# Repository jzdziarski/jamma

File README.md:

# /jamma
## Arcade JAMMA adapters and interface boards 
License: For non-commercial educational use only

|Subfolder|Description|
|--------------------------------|------------------------------------|
|CAD|PCB CAD Files|
|BOM|Bill of Materials (CSV)|
|Microcode|Microcontroller Code|
|Renderings|PCB Renderings|

## PCB Library
|Platform|Title|Tag|Status|
|-------------------|------------|-------------------------|----------|  
|Atari System I	|RoadBlasters|ROADBLASTERS_REV_0|Release|
|Atari System I |RoadBlasters|ROADBLASTERS_REV_1|Release|
|Atari System I/II/68K |*|ATARI_REV_0|Release|
|Atari System I/II/68K |*|ATARI_REV_1|Release|
|Blasteroids |Blasteroids|BLASTEROIDS_REV_0|Release|
|Midway MCR III	|Spy Hunter|SPY_HUNTER_REV_0|Release|
|Midway MCR III	|Spy Hunter|SPY_HUNTER_REV_1|Release|
|Midway MCR III |Spy Hunter|SPY_HUNTER_REV_1.1|Development|
|Midway MCR II	|TRON|TRON_REV_0|Release|
|Midway MCR II	|TRON|TRON_REV_1|Release|
|SEGA Super Scaler|Outrun|OUTRUN_REV_0|Release|
|SEGA Super Scaler|Super Hang-On|SUPER_HANG_ON_REV_0|Development|
|Williams System	|*|WILLIAMS_REV_0|Release|
|Williams System        |*|WILLIAMS_REV_1|Development|
|Universal Edge	|*|UNIVERSAL_EDGE|Release|
|Universal Interface|*|UNIVERSAL_INTERFACE|Release|
|Universal Microcontroller Interface|*|UNIVERSAL_MICROCONTROLLER|Template|
|Universal Microcontroller Adapter|*|UNIVERSAL_MICROCONTROLLER_ADAPTER|Template|

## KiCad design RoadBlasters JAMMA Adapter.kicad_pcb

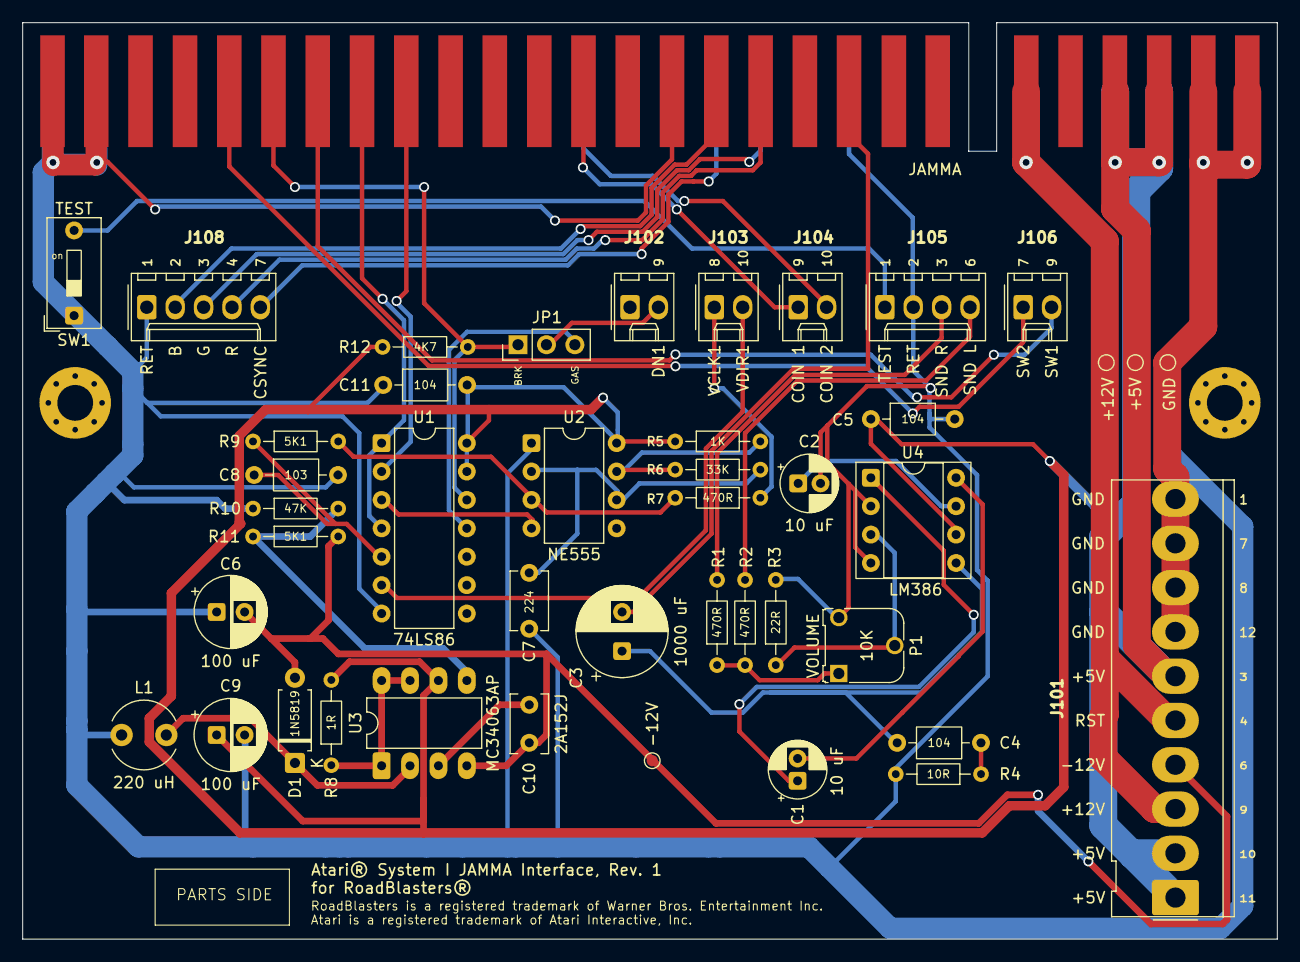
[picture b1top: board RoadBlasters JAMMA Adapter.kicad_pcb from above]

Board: 2 copper layers, 112.2 x 82.0 mm, 46 parts (0 on the bottom side), 39 nets.

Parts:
+5V: TP2; TestPoint_Pad_D1.0mm
+12V: TP3; TestPoint_Pad_D1.0mm
-12V: TP4; TestPoint_Pad_D1.0mm
C1, C2: 10 uF; CP_Radial_D5.0mm_P2.00mm
C3: 1000 uF; CP_Radial_D8.0mm_P3.50mm
C4, C5, C11: 104; C_Axial_L3.8mm_D2.6mm_P7.50mm_Horizontal
C6, C9: 100 uF; CP_Radial_D6.3mm_P2.50mm
C7: 224; C_Disc_D5.1mm_W3.2mm_P5.00mm
C8: 103; C_Axial_L3.8mm_D2.6mm_P7.50mm_Horizontal
C10: 2A152J; C_Disc_D5.1mm_W3.2mm_P3.4mm
D1: 1N5819; D_A-405_P7.62mm_Horizontal
GND: TP1; TestPoint_Pad_D1.0mm
J101: Molex_KK-396_5273-10A_1x10_P3.96mm_Vertical
J102, J103, J104, J106: Molex_KK-254_AE-6410-02A_1x02_P2.54mm_Vertical
J105: Molex_KK-254_AE-6410-04A_1x04_P2.54mm_Vertical
J108: Molex_KK-254_AE-6410-05A_1x05_P2.54mm_Vertical
JAMMA: HDR_JAMMA_56P_EDGE_CONNECTOR
JP1: PinHeader_1x03_P2.54mm_Vertical
L1: 220 uH; L_Radial_D6.0mm_P4.00mm
P1: 10K; Potentiometer_Runtron_RM-065_Vertical
PMH1, PMH4: MountingHole_3.2mm_M3_Pad_Via
R1: R1; R_Axial_DIN0204_L3.6mm_D1.6mm_P7.62mm_Horizontal
R2, R7: 470R; R_Axial_DIN0204_L3.6mm_D1.6mm_P7.62mm_Horizontal
R3: 22R; R_Axial_DIN0204_L3.6mm_D1.6mm_P7.62mm_Horizontal
R4: R_Axial_DIN0204_L3.6mm_D1.6mm_P7.62mm_Horizontal
R5: 1K; R_Axial_DIN0204_L3.6mm_D1.6mm_P7.62mm_Horizontal
R6: 33K; R_Axial_DIN0204_L3.6mm_D1.6mm_P7.62mm_Horizontal
R8: 1R; R_Axial_DIN0204_L3.6mm_D1.6mm_P7.62mm_Horizontal
R9, R11: 5K1; R_Axial_DIN0204_L3.6mm_D1.6mm_P7.62mm_Horizontal
R10: 47K; R_Axial_DIN0204_L3.6mm_D1.6mm_P7.62mm_Horizontal
R12: 4K7; R_Axial_DIN0204_L3.6mm_D1.6mm_P7.62mm_Horizontal
TEST: SW1; SW_DIP_SPSTx01_Slide_9.78x4.72mm_W7.62mm_P2.54mm
U1: 74LS86; DIP-14_W7.62mm
U2: NE555; DIP-8_W7.62mm
U3: MC34063AP; DIP-8_W7.62mm_LongPads
U4: LM386; DIP-8_W7.62mm_Socket

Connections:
1P_B1: J106.2, JAMMA.22
1P_B2: JAMMA.23, JP1.1, R12.2, U1.12
1P_B2_OUT: J102.2, JP1.2
1P_B3: J106.1, JAMMA.24
1P_L: JAMMA.20, U1.2
1P_R: JAMMA.21, U1.1, U1.4
!1P_B2: JP1.3, U1.11
+5V: +5V.1, C5.1, C9.1, C11.2, J101.1, J101.2, J101.6, JAMMA.3, JAMMA.4, JAMMA.C, JAMMA.D, R5.1, R8.2, R12.1, U1.13, U1.14, U2.8, U3.6, U4.6
+12V: +12V.1, J101.3, J101.5, JAMMA.6, JAMMA.F
-12V: -12V.1, C6.2, C10.1, D1.2, J101.4, R11.2, U3.4
AUDIO_L: J105.4, R2.2
AUDIO_MONO: P1.1, R1.1, R2.1
AUDIO_OUT: C3.2, JAMMA.10
AUDIO_PREAMP: P1.2, R3.1, U4.3
AUDIO_PREAMP_OUT: C3.1, C4.2, U4.5
AUDIO_R: J105.3, R1.2
C4_R4: C4.1, R4.1
CINV_R10_R9: R10.2, R11.1, U3.5
COIN_1: J104.1, JAMMA.16
COIN_2: J104.2, JAMMA.T
GND: C2.2, C5.2, C6.1, C7.1, C8.2, C9.2, C11.1, GND.1, J101.7, J101.8, J101.9, J101.10, J105.2, J108.1, JAMMA.1, JAMMA.2, JAMMA.14, JAMMA.27, JAMMA.28, JAMMA.A, JAMMA.B, JAMMA.L, JAMMA.e, JAMMA.f, L1.1, P1.3, R3.2, R4.2, R10.1, TEST.1, U1.7, U2.1, U4.2, U4.4
R8: R8.1, U3.1, U3.7, U3.8
SWE: D1.1, L1.2, U3.2
TEST_SW: J105.1, TEST.2
U2_DIS: R5.2, R6.1, U2.7
U2_RESET: U1.3, U2.4
U2_THR: C7.2, R6.2, U2.2, U2.6
U3_CAP: C10.2, U3.3
U4_BYPASS: C2.1, U4.7
U4_GAIN_P1: C1.1, U4.1
U4_GAIN_P8: C1.2, U4.8
VCLK1: R7.2, R9.2, U2.3
VCLK1_DELAYED: C8.1, R9.1, U1.5
VCLK1_OUT: J103.1, R7.1
VDIR1_OUT: J103.2, U1.6
VIDEO_B: J108.2, JAMMA.13
VIDEO_G: J108.3, JAMMA.N
VIDEO_R: J108.4, JAMMA.12
VIDEO_SYNC: J108.5, JAMMA.P

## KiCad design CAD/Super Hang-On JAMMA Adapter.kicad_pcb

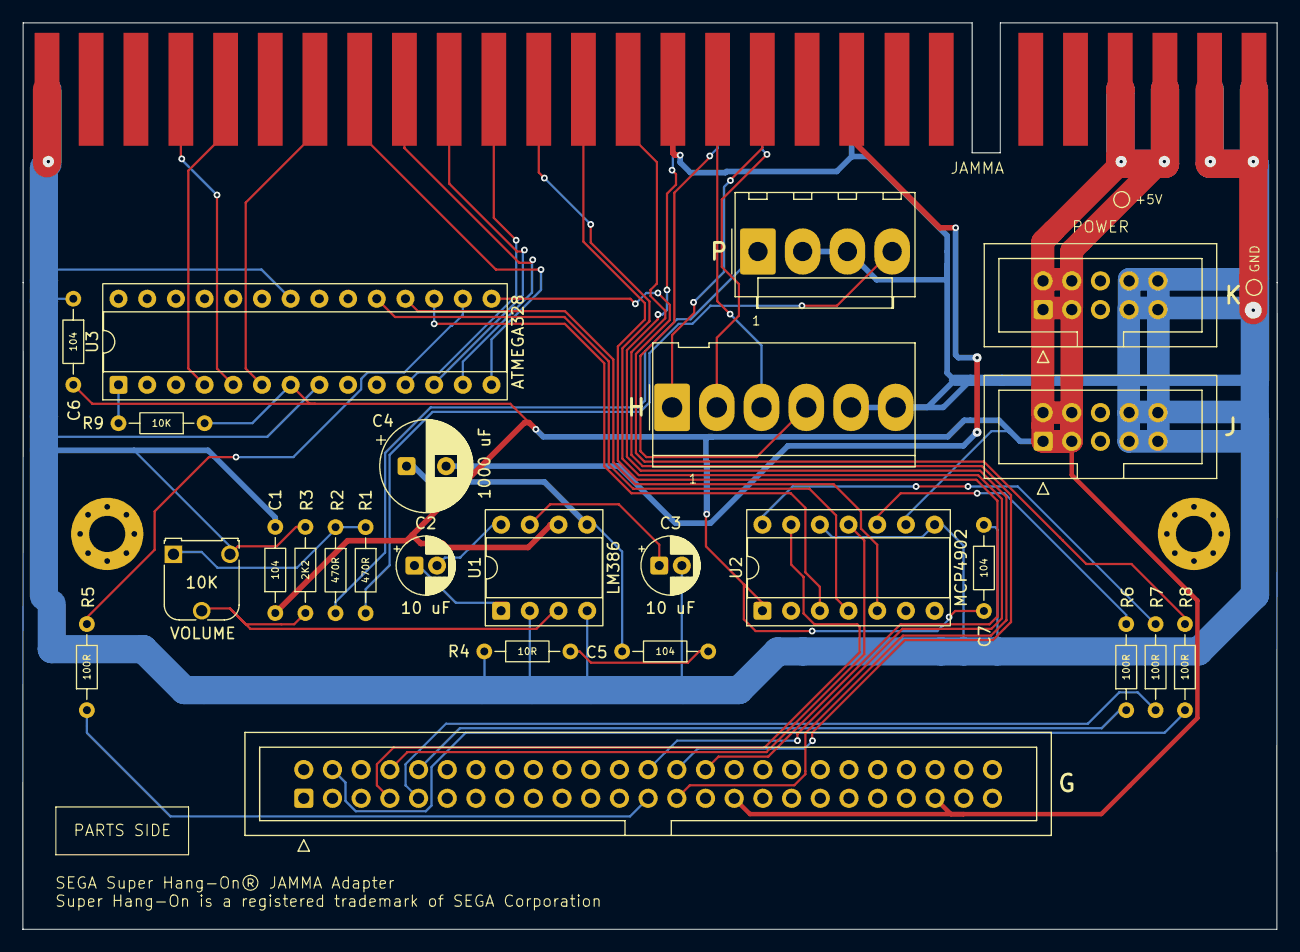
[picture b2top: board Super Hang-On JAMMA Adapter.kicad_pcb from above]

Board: 2 copper layers, 111.0 x 80.2 mm, 28 parts (0 on the bottom side), 41 nets.

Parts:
+5V: TestPoint_Pad_D1.0mm
C1, C5, C6, C7: 104; R_Axial_DIN0204_L3.6mm_D1.6mm_P7.62mm_Horizontal
C2, C3: 10 uF; CP_Radial_D5.0mm_P2.00mm
C4: 1000 uF; CP_Radial_D8.0mm_P3.50mm
G: G; IDC-Header_2x25_P2.54mm_Vertical
GND: TestPoint_Pad_D1.0mm
H: H; Molex_KK-396_5273-06A_1x06_P3.96mm_Vertical
J: J; IDC-Header_2x05_P2.54mm_Vertical
JAMMA: HDR_JAMMA_56P_EDGE_CONNECTOR
K: K; IDC-Header_2x05_P2.54mm_Vertical
P: P; Molex_KK-396_A-41791-0004_1x04_P3.96mm_Vertical
R1, R2: 470R; R_Axial_DIN0204_L3.6mm_D1.6mm_P7.62mm_Horizontal
R3: 2K2; R_Axial_DIN0204_L3.6mm_D1.6mm_P7.62mm_Horizontal
R4: 10R; R_Axial_DIN0204_L3.6mm_D1.6mm_P7.62mm_Horizontal
R5, R6, R7, R8: 100R; R_Axial_DIN0204_L3.6mm_D1.6mm_P7.62mm_Horizontal
R9: 10K; R_Axial_DIN0204_L3.6mm_D1.6mm_P7.62mm_Horizontal
U1: LM386; DIP-8_W7.62mm_Socket
U2: MCP4902; DIP-14_W7.62mm_Socket
U3: ATMEGA328; DIP-28_W7.62mm_Socket
VOLUME: 10K; Potentiometer_Runtron_RM-065_Vertical

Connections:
1P_B1: JAMMA.22, U3.6
1P_B3: JAMMA.24, U3.4
1P_B4: JAMMA.25, U3.5
1P_D: JAMMA.19, U3.12
1P_L: JAMMA.20, U3.13
1P_R: JAMMA.21, U3.14
1P_START: G.26, JAMMA.17
1P_U: JAMMA.18, U3.11
+5V: +5V.1, C1.1, C6.2, C7.2, G.31, G.45, J.1, J.2, J.3, J.4, JAMMA.3, JAMMA.4, JAMMA.C, JAMMA.D, K.1, K.2, K.3, K.4, R9.1, U1.6, U2.1, U2.9, U3.7
ACCEL: G.9, R7.1
AUDIO_L: P.1, R2.2
AUDIO_MONO: R1.1, R2.1, VOLUME.1
AUDIO_R: P.4, R1.2
BRK: G.4, R8.1
C5_R4: C5.1, R4.1
COIN_1: G.30, JAMMA.16
GND: C1.2, C3.2, C6.1, C7.1, GND.1, H.5, H.6, J.7, J.8, J.9, J.10, JAMMA.1, JAMMA.2, JAMMA.14, JAMMA.28, JAMMA.A, JAMMA.B, JAMMA.L, JAMMA.f, K.7, K.8, K.9, K.10, P.2, P.3, R3.2, R4.2, U1.2, U1.4, U2.8, U2.12, U3.8, U3.22, VOLUME.3
PB1: R8.2, U3.15
PB2: R5.2, U3.16
PREAMP: R3.1, U1.3, VOLUME.2
PREAMP_OUT: C4.1, C5.2, U1.5
REFA: G.7, U2.13
REFB: G.8, U2.11
SERVICE: G.27, JAMMA.R
SPKR+: C4.2, JAMMA.10
STEER: G.10, R6.1
TEST: G.28, JAMMA.15
TURBO: G.25, R5.1
U1_BYPASS: C3.1, U1.7
U1_GAIN_P1: C2.1, U1.1
U1_GAIN_P8: C2.2, U1.8
U3_MISO_U2_SDI: U2.5, U3.18
U3_MOSI_U2_CS: U2.3, U3.17
U3_RSET: R9.2, U3.1
U3_SCK_U2_SCK: U2.4, U3.19
VID_B: H.3, JAMMA.13
VID_CSYNC: H.4, JAMMA.P
VID_G: H.2, JAMMA.N
VID_R: H.1, JAMMA.12
VOUTA: R7.2, U2.14
VOUTB: R6.2, U2.10

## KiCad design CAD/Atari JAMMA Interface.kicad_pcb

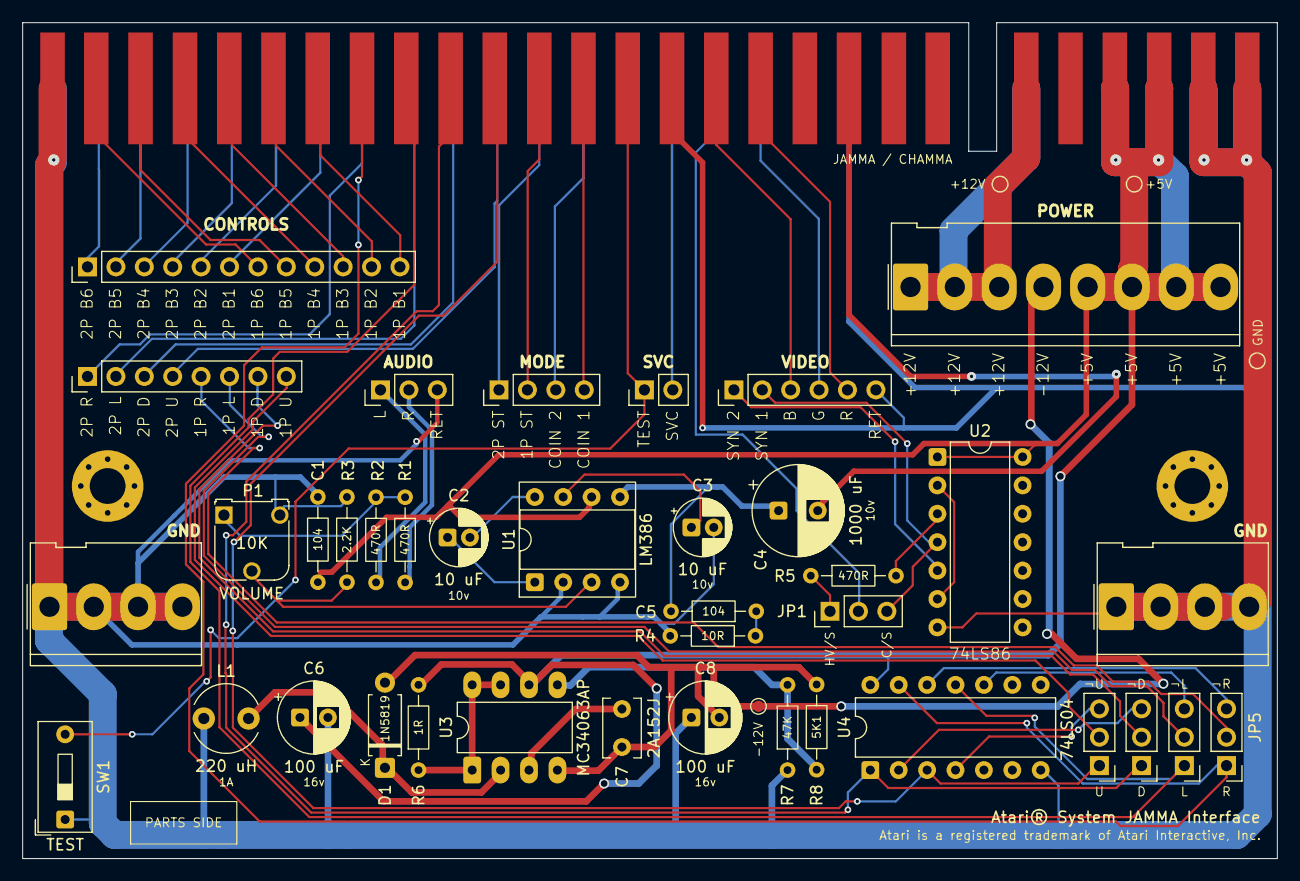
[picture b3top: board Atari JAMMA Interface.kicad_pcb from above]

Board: 2 copper layers, 112.2 x 74.8 mm, 43 parts (0 on the bottom side), 61 nets.

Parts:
+5V, +12V: TestPoint_Pad_D1.0mm
-12V: TestPoint_Pad_D1.0mm
AUDIO: PinHeader_1x03_P2.54mm_Vertical
C1, C5: 104; R_Axial_DIN0204_L3.6mm_D1.6mm_P7.62mm_Horizontal
C2, C3: 10 uF; CP_Radial_D5.0mm_P2.00mm
C4: 1000 uF; CP_Radial_D8.0mm_P3.50mm
C6, C8: 100 uF; CP_Radial_D6.3mm_P2.50mm
C7: 2A152J; C_Disc_D5.1mm_W3.2mm_P3.4mm
CONTROLS: PinHeader_1x12_P2.54mm_Vertical
D1: 1N5819; D_A-405_P7.62mm_Horizontal
DIRECTIONALS: PinHeader_1x08_P2.54mm_Vertical
GND: TestPoint_Pad_D1.0mm
GND#2, GND#3: Molex_KK-396_5273-04A_1x04_P3.96mm_Vertical
HV/S: PinHeader_1x03_P2.54mm_Vertical
HV/S#2, HV/S#3, HV/S#4, HV/S#5: PinHeader_1x03_P2.54mm_Vertical
JAMMA / CHAMMA: HDR_JAMMA_56P_EDGE_CONNECTOR
L1: 220 uH; L_Radial_D6.0mm_P4.00mm
MODE: PinHeader_1x04_P2.54mm_Vertical
P1: 10K; Potentiometer_Runtron_RM-065_Vertical
POWER: Molex_KK-396_5273-08A_1x08_P3.96mm_Vertical
R1, R2, R5: 470R; R_Axial_DIN0204_L3.6mm_D1.6mm_P7.62mm_Horizontal
R3: 2.2K; R_Axial_DIN0204_L3.6mm_D1.6mm_P7.62mm_Horizontal
R4: 10R; R_Axial_DIN0204_L3.6mm_D1.6mm_P7.62mm_Horizontal
R6: 1R; R_Axial_DIN0204_L3.6mm_D1.6mm_P7.62mm_Horizontal
R7: 47K; R_Axial_DIN0204_L3.6mm_D1.6mm_P7.62mm_Horizontal
R8: 5K1; R_Axial_DIN0204_L3.6mm_D1.6mm_P7.62mm_Horizontal
SVC: PinHeader_1x02_P2.54mm_Vertical
TEST: SW1; SW_DIP_SPSTx01_Slide_9.78x4.72mm_W7.62mm_P2.54mm
U1: LM386; DIP-8_W7.62mm_Socket
U2: DIP-14_W7.62mm
U3: MC34063AP; DIP-8_W7.62mm_LongPads
U4: 74LS04; DIP-14_W7.62mm
VIDEO: PinHeader_1x06_P2.54mm_Vertical

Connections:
1P_!D: HV/S#5.3, U4.2
1P_!L: HV/S.3, U4.10
1P_!R: HV/S#2.3, U4.12
1P_!U: HV/S#3.3, U4.4
1P_B1: CONTROLS.12, JAMMA / CHAMMA.22
1P_B2: CONTROLS.11, JAMMA / CHAMMA.23
1P_B3: CONTROLS.10, JAMMA / CHAMMA.24
1P_B4: CONTROLS.9, JAMMA / CHAMMA.25
1P_B5: CONTROLS.8, JAMMA / CHAMMA.26
1P_B6: CONTROLS.7, JAMMA / CHAMMA.27
1P_D: HV/S#5.1, JAMMA / CHAMMA.19, U4.1
1P_D_OUT: DIRECTIONALS.7, HV/S#5.2
1P_L: HV/S.1, JAMMA / CHAMMA.20, U4.11
1P_L_OUT: DIRECTIONALS.6, HV/S.2
1P_R: HV/S#2.1, JAMMA / CHAMMA.21, U4.13
1P_R_OUT: DIRECTIONALS.5, HV/S#2.2
1P_START: JAMMA / CHAMMA.17, MODE.2
1P_U: HV/S#3.1, JAMMA / CHAMMA.18, U4.3
1P_U_OUT: DIRECTIONALS.8, HV/S#3.2
2P_B1: CONTROLS.6, JAMMA / CHAMMA.Z
2P_B2: CONTROLS.5, JAMMA / CHAMMA.a
2P_B3: CONTROLS.4, JAMMA / CHAMMA.b
2P_B4: CONTROLS.3, JAMMA / CHAMMA.c
2P_B5: CONTROLS.2, JAMMA / CHAMMA.d
2P_B6: CONTROLS.1, JAMMA / CHAMMA.e
2P_D: DIRECTIONALS.3, JAMMA / CHAMMA.W
2P_L: DIRECTIONALS.2, JAMMA / CHAMMA.X
2P_R: DIRECTIONALS.1, JAMMA / CHAMMA.Y
2P_START: JAMMA / CHAMMA.U, MODE.1
2P_U: DIRECTIONALS.4, JAMMA / CHAMMA.V
+5V: +5V.1, C1.1, C6.1, JAMMA / CHAMMA.3, JAMMA / CHAMMA.4, JAMMA / CHAMMA.C, JAMMA / CHAMMA.D, POWER.5, POWER.6, POWER.7, POWER.8, R6.2, U1.6, U2.1, U2.14, U3.6, U4.14
+12V: +12V.1, JAMMA / CHAMMA.6, JAMMA / CHAMMA.F, POWER.1, POWER.2, POWER.3
-12V: -12V.1, C7.1, C8.2, D1.2, POWER.4, R8.2, U3.4
AUDIO_L: AUDIO.1, R2.2
AUDIO_MONO: P1.1, R1.1, R2.1
AUDIO_R: AUDIO.2, R1.2
C5_R4: C5.1, R4.1
CINV_R10_R9: R7.2, R8.1, U3.5
COIN_1: JAMMA / CHAMMA.16, MODE.4
COIN_2: JAMMA / CHAMMA.T, MODE.3
GND: AUDIO.3, C1.2, C3.2, C6.2, C8.1, GND.1, GND#2.1, GND#2.2, GND#2.3, GND#2.4, GND#3.1, GND#3.2, GND#3.3, GND#3.4, JAMMA / CHAMMA.1, JAMMA / CHAMMA.2, JAMMA / CHAMMA.14, JAMMA / CHAMMA.28, JAMMA / CHAMMA.A, JAMMA / CHAMMA.B, JAMMA / CHAMMA.L, JAMMA / CHAMMA.f, L1.1, P1.3, R3.2, R4.2, R7.1, TEST.1, U1.2, U1.4, U2.7, U4.7, VIDEO.6
PREAMP: P1.2, R3.1, U1.3
PREAMP_OUT: C4.1, C5.2, U1.5
R8: R6.1, U3.1, U3.7, U3.8
SERVICE: JAMMA / CHAMMA.R, SVC.2
SPKR+: C4.2, JAMMA / CHAMMA.10
SWE: D1.1, L1.2, U3.2
TEST: JAMMA / CHAMMA.15, SVC.1, TEST.2
U3_CAP: C7.2, U3.3
U4_BYPASS: C3.1, U1.7
U4_GAIN_P1: C2.1, U1.1
U4_GAIN_P8: C2.2, U1.8
VID_B: JAMMA / CHAMMA.13, VIDEO.3
VID_CSYNC: HV/S#4.2, JAMMA / CHAMMA.P
VID_G: JAMMA / CHAMMA.N, VIDEO.4
VID_NXOR: HV/S#4.1, R5.1
VID_NXOR_R5: R5.2, U2.3
VID_R: JAMMA / CHAMMA.12, VIDEO.5
VID_SYN1: HV/S#4.3, U2.4, VIDEO.2
VID_SYN2: U2.5, VIDEO.1
VID_XOR: U2.2, U2.6

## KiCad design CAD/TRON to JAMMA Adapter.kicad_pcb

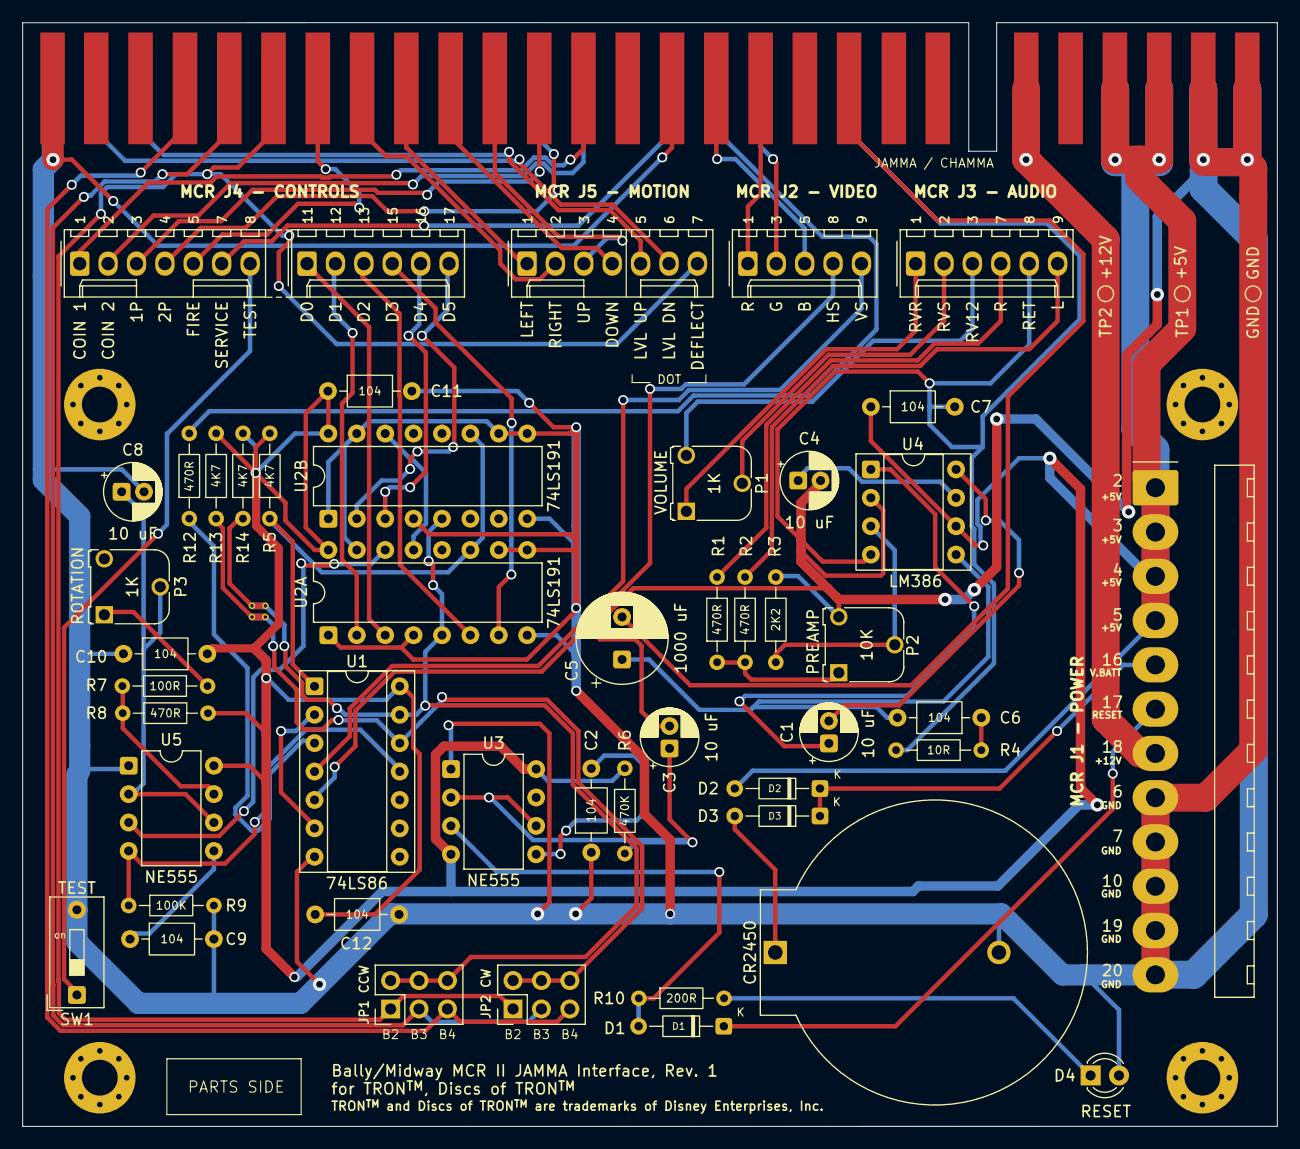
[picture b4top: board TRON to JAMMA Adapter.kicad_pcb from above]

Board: 2 copper layers, 112.2 x 98.7 mm, 56 parts (0 on the bottom side), 63 nets.

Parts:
+5V: TP1; TestPoint_Pad_D1.0mm
+12V: TP2; TestPoint_Pad_D1.0mm
C1, C3, C4, C8: 10 uF; CP_Radial_D5.0mm_P2.00mm
C2, C6, C7, C9, C10, C11, C12: 104; C_Axial_L3.8mm_D2.6mm_P7.50mm_Horizontal
C5: 1000 uF; CP_Radial_D8.0mm_P3.80mm
CR2450: BatteryHolder_ComfortableElectronic_CH273-2450_1x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; BatteryHolder_ComfortableElectronic_CH273-2450_1x2450
D1: 1N4148; D_DO-34_SOD68_P7.62mm_Horizontal
D2, D3: 1N5817; D_DO-34_SOD68_P7.62mm_Horizontal
D4: LED; LED_D3.0mm
GND: GND; TestPoint_Pad_D1.0mm
JAMMA / CHAMMA: HDR_JAMMA_56P_EDGE_CONNECTOR
JP1 CCW, JP2 CW: PinHeader_2x03_P2.54mm_Vertical
MCRJ1: Molex_KK-396_A-41792-0012_1x12_P3.96mm_Horizontal
MCRJ2: Molex_KK-254_AE-6410-05A_1x05_P2.54mm_Vertical
MCRJ3, MCRJ4B: Molex_KK-254_AE-6410-06A_1x06_P2.54mm_Vertical
MCRJ4A, MCRJ5: Molex_KK-254_AE-6410-07A_1x07_P2.54mm_Vertical
P1, P3: 1K; Potentiometer_Runtron_RM-065_Vertical
P2: 10K; Potentiometer_Runtron_RM-065_Vertical
PMH1, PMH2, PMH3, PMH4: MountingHole_3.2mm_M3_Pad_Via
R1, R2, R8, R12: 470R; R_Axial_DIN0204_L3.6mm_D1.6mm_P7.62mm_Horizontal
R3: 2K2; R_Axial_DIN0204_L3.6mm_D1.6mm_P7.62mm_Horizontal
R4: 10R; R_Axial_DIN0204_L3.6mm_D1.6mm_P7.62mm_Horizontal
R5, R13, R14: 4K7; R_Axial_DIN0204_L3.6mm_D1.6mm_P7.62mm_Horizontal
R6: 470K; R_Axial_DIN0204_L3.6mm_D1.6mm_P7.62mm_Horizontal
R7: 100R; R_Axial_DIN0204_L3.6mm_D1.6mm_P7.62mm_Horizontal
R9: 100K; R_Axial_DIN0204_L3.6mm_D1.6mm_P7.62mm_Horizontal
R10: 200R; R_Axial_DIN0204_L3.6mm_D1.6mm_P7.62mm_Horizontal
TEST: SW1; SW_DIP_SPSTx01_Slide_9.78x4.72mm_W7.62mm_P2.54mm
U1: 74LS86; DIP-14_W7.62mm_Socket
U2A, U2B: 74LS191; DIP-16_W7.62mm
U3, U5: NE555; DIP-8_W7.62mm
U4: LM386; DIP-8_W7.62mm_Socket

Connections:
1P_B1: JAMMA / CHAMMA.22, MCRJ4A.5
1P_B2: JAMMA / CHAMMA.23, JP1 CCW.1, JP2 CW.1, MCRJ5.7
1P_B3: JAMMA / CHAMMA.24, JP1 CCW.3, JP2 CW.3
1P_B4: JAMMA / CHAMMA.25, JP1 CCW.5, JP2 CW.5
1P_B5: JAMMA / CHAMMA.d, MCRJ5.5
1P_B6: JAMMA / CHAMMA.e, MCRJ5.6
1P_D: JAMMA / CHAMMA.19, MCRJ5.4
1P_L: JAMMA / CHAMMA.20, MCRJ5.1
1P_R: JAMMA / CHAMMA.21, MCRJ5.2
1P_START: JAMMA / CHAMMA.17, MCRJ4A.3
1P_U: JAMMA / CHAMMA.18, MCRJ5.3
2P_START: JAMMA / CHAMMA.U, MCRJ4A.4
+5V: +5V.1, C7.1, C10.2, C11.1, C12.2, D2.2, JAMMA / CHAMMA.3, JAMMA / CHAMMA.4, JAMMA / CHAMMA.C, JAMMA / CHAMMA.D, MCRJ1.1, MCRJ1.2, MCRJ1.3, MCRJ1.4, R5.2, R6.2, R8.2, R13.2, R14.2, U1.14, U2A.16, U2B.16, U3.4, U3.8, U4.6, U5.8
+5V_R5: R5.1, U1.1, U2A.11, U2B.11
+12V_IN: +12V.1, JAMMA / CHAMMA.6, JAMMA / CHAMMA.F, MCRJ1.7
AUDIO_L: MCRJ3.6, R2.2
AUDIO_MONO: P2.1, R1.1, R2.1
AUDIO_OUT: C5.2, JAMMA / CHAMMA.10
AUDIO_PREAMP: P2.2, R3.1, U4.3
AUDIO_PREAMP_OUT: C5.1, C6.2, U4.5
AUDIO_R: MCRJ3.4, R1.2
BATTERY: CR2450.1, D3.2
C6_R4: C6.1, R4.1
CCW_IN: JP1 CCW.2, JP1 CCW.4, JP1 CCW.6, U1.13, U2A.5, U2B.5
CLK: U2A.14, U5.3
CLK_GATE: R9.1, U1.11, U5.4
COIN_1: JAMMA / CHAMMA.16, MCRJ4A.1
COIN_2: JAMMA / CHAMMA.T, MCRJ4A.2
CW_IN: JP2 CW.2, JP2 CW.4, JP2 CW.6, U1.12
E1: MCRJ4B.1, U2A.3
E2: MCRJ4B.2, U2A.2
E3: MCRJ4B.3, U2A.6
E4: MCRJ4B.4, U2A.7
E5: MCRJ4B.5, U2B.3
E6: MCRJ4B.6, U2B.2
GND: C2.1, C3.2, C4.2, C7.2, C8.2, C9.2, C10.1, C11.2, C12.1, CR2450.2, D4.2, GND.1, JAMMA / CHAMMA.1, JAMMA / CHAMMA.2, JAMMA / CHAMMA.14, JAMMA / CHAMMA.28, JAMMA / CHAMMA.A, JAMMA / CHAMMA.B, JAMMA / CHAMMA.L, JAMMA / CHAMMA.f, MCRJ1.8, MCRJ1.9, MCRJ1.10, MCRJ1.11, MCRJ1.12, MCRJ3.5, P2.3, R3.2, R4.2, R9.2, TEST.2, U1.7, U2A.1, U2A.4, U2A.8, U2A.9, U2A.10, U2A.15, U2B.1, U2B.4, U2B.8, U2B.9, U2B.10, U2B.15, U3.1, U4.2, U4.4, U5.1
R6_U3_P2_P6: C3.1, R6.1, U3.2, U3.6
RESET_5V: D1.2, R10.1, U3.3
RESET_5V_OUT: D1.1, MCRJ1.6
RESET_LED: D4.1, R10.2
SERVICE_SW: JAMMA / CHAMMA.R, MCRJ4A.6
TEST_SW: MCRJ4A.7, TEST.1
U1_P6_U1_P2: U1.2, U1.6
U3_CTRL: C2.2, U3.5
U4_BYPASS: C4.1, U4.7
U4_GAIN_P1: C1.1, U4.1
U4_GAIN_P8: C1.2, U4.8
U5_CTRL: C9.1, U5.5
U5_DIS: R7.1, R8.1, U5.7
U5_DIS_R2: P3.1, R7.2
U5_TRIG: C8.1, P3.2, U5.2, U5.6
U6_RCO: U2A.13, U2B.14
V.BATT: D2.1, D3.1, MCRJ1.5
VIDEO_B: JAMMA / CHAMMA.13, MCRJ2.3
VIDEO_G: JAMMA / CHAMMA.N, MCRJ2.2
VIDEO_HSYNC: MCRJ2.4, U1.5
VIDEO_RED: JAMMA / CHAMMA.12, MCRJ2.1
VIDEO_SYNC: JAMMA / CHAMMA.P, R12.2
VIDEO_SYNC_R12: R12.1, U1.3
VIDEO_VSYNC: MCRJ2.5, U1.4
VOL_GND: MCRJ3.3, P1.3
VOL_IN: MCRJ3.1, P1.1
VOL_OUT: MCRJ3.2, P1.2

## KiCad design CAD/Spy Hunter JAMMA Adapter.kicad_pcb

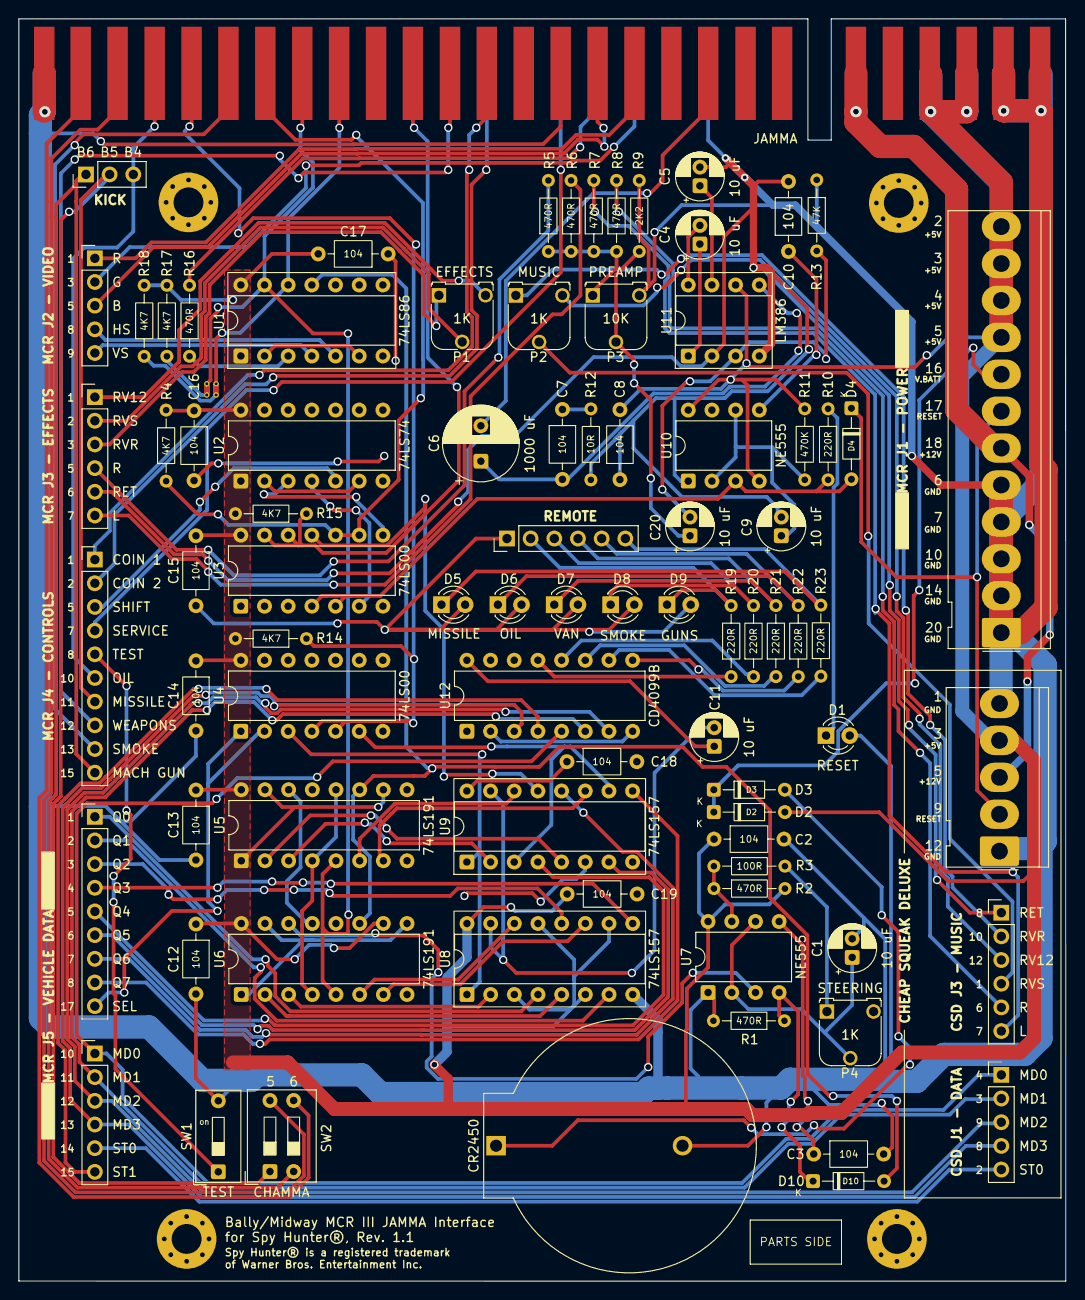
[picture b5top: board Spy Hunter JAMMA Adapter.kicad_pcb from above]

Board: 2 copper layers, 112.3 x 135.4 mm, 88 parts (0 on the bottom side), 102 nets.

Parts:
C1, C4, C5, C9, C11, C20: 10 uF; CP_Radial_D5.0mm_P2.00mm
C2, C3, C7, C8, C10, C12, C13, C14, C15, C16, C17, C18, C19: 104; C_Axial_L3.8mm_D2.6mm_P7.50mm_Horizontal
C6: 1000 uF; CP_Radial_D8.0mm_P3.80mm
CR2450: BatteryHolder_ComfortableElectronic_CH273-2450_1x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; BatteryHolder_ComfortableElectronic_CH273-2450_1x2450
CSDJ1: PinHeader_1x05_P2.54mm_Vertical
CSDJ2: Molex_KK-396_5273-05A_1x05_P3.96mm_Vertical
CSDJ3: PinHeader_1x06_P2.54mm_Vertical
D1, D5, D6, D7, D8, D9: LED; LED_D3.0mm
D2, D3: 1N5817; D_DO-34_SOD68_P7.62mm_Horizontal
D4, D10: 1N4148; D_DO-34_SOD68_P7.62mm_Horizontal
JAMMA: HDR_JAMMA_56P_EDGE_CONNECTOR
KICK: PinHeader_1x03_P2.54mm_Vertical
MCR J5 - LAMPS: PinHeader_1x06_P2.54mm_Vertical
MCRJ1: Molex_KK-396_5273-12A_1x12_P3.96mm_Vertical
MCRJ2: PinHeader_1x05_P2.54mm_Vertical
MCRJ3: PinHeader_1x06_P2.54mm_Vertical
MCRJ4: PinHeader_1x10_P2.54mm_Vertical
MCRJ5: PinHeader_1x09_P2.54mm_Vertical
P1, P2, P4: 1K; Potentiometer_Runtron_RM-065_Vertical
P3: 10K; Potentiometer_Runtron_RM-065_Vertical
PMH1, PMH2, PMH3, PMH4: MountingHole_3.2mm_M3_Pad_Via
R1, R2, R5, R6, R7, R8, R16: 470R; R_Axial_DIN0204_L3.6mm_D1.6mm_P7.62mm_Horizontal
R3: 100R; R_Axial_DIN0204_L3.6mm_D1.6mm_P7.62mm_Horizontal
R4, R14, R15, R17, R18: 4K7; R_Axial_DIN0204_L3.6mm_D1.6mm_P7.62mm_Horizontal
R9: 2K2; R_Axial_DIN0204_L3.6mm_D1.6mm_P7.62mm_Horizontal
R10, R19, R20, R21, R22, R23: 220R; R_Axial_DIN0204_L3.6mm_D1.6mm_P7.62mm_Horizontal
R11: 470K; R_Axial_DIN0204_L3.6mm_D1.6mm_P7.62mm_Horizontal
R12: 10R; R_Axial_DIN0204_L3.6mm_D1.6mm_P7.62mm_Horizontal
R13: 47K; R_Axial_DIN0204_L3.6mm_D1.6mm_P7.62mm_Horizontal
REMOTE: PinHeader_1x06_P2.54mm_Vertical
SW2: SW_DIP_SPSTx02_Slide_9.78x7.26mm_W7.62mm_P2.54mm
TEST: SW1; SW_DIP_SPSTx01_Slide_9.78x4.72mm_W7.62mm_P2.54mm
U1: 74LS86; DIP-14_W7.62mm_Socket
U2: 74LS74; DIP-14_W7.62mm
U3, U4: 74LS00; DIP-14_W7.62mm
U5, U6: 74LS191; DIP-16_W7.62mm
U7, U10: NE555; DIP-8_W7.62mm
U8, U9: 74LS157; DIP-16_W7.62mm_Socket
U11: LM386; DIP-8_W7.62mm_Socket
U12: CD4099B; DIP-16_W7.62mm

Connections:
1P_B1: JAMMA.22, R4.1, U3.9, U3.10
1P_B2: JAMMA.23, MCRJ4.9
1P_B3: JAMMA.24, R14.1, U4.4, U4.5
1P_B4: JAMMA.25, KICK.3, MCRJ4.6
1P_B5: KICK.2, MCRJ4.7, SW2.1
1P_B5_CHAMMA: JAMMA.26, SW2.4
1P_B6: KICK.1, MCRJ4.10, SW2.2
1P_B6_CHAMMA: JAMMA.27, SW2.3
1P_GAS: U4.6, U9.3, U9.10
1P_LEFT: JAMMA.20, U1.12
1P_RIGHT: JAMMA.21, U1.13, U5.5, U6.5
1P_START: JAMMA.17, MCRJ4.8
1P_TURBO: U3.11, U9.13
1P_U: JAMMA.18, R15.1, U3.12, U3.13
!RST: U2.4, U3.6
!SEL: U4.3, U8.1, U9.1
!SHIFT_LATCH: U2.2, U2.6
+5V: C2.1, C8.2, C11.1, C12.1, C13.1, C14.1, C15.1, C16.1, C17.2, C18.1, C19.1, CSDJ2.4, D2.2, JAMMA.3, JAMMA.4, JAMMA.C, JAMMA.D, MCRJ1.9, MCRJ1.10, MCRJ1.11, MCRJ1.12, R2.2, R4.2, R11.2, R14.2, R15.2, R17.2, R18.2, U1.1, U1.14, U2.1, U2.14, U3.14, U4.14, U5.1, U5.10, U5.15, U5.16, U6.10, U6.16, U7.8, U8.3, U8.6, U8.10, U8.13, U8.16, U9.6, U9.16, U10.4, U10.8, U11.6, U12.16
+5V_RST: CSDJ2.2, D4.1, MCRJ1.7
+12V: CSDJ2.3, JAMMA.6, JAMMA.F, MCRJ1.6
AUDIO_MONO: P3.1, R5.1, R6.1, R7.1, R8.1
AUDIO_OUT: C6.2, JAMMA.10
AUDIO_PREAMP: C20.1, P3.2, R9.1
AUDIO_PREAMP_COUPLED: C20.2, R13.2, U11.3
AUDIO_PREAMP_OUT: C6.1, C7.2, U11.5
BATT+: CR2450.1, D3.2
C7_R12: C7.1, R12.1
CLK: U6.14, U7.3
CLK_GATE: D10.2, U1.11, U5.11, U6.11
COIN_1: JAMMA.16, MCRJ4.1
COIN_2: JAMMA.T, MCRJ4.2
D5: D5.1, R23.2, REMOTE.6
D6: D6.1, R22.2, REMOTE.5
D7: D7.1, R21.2, REMOTE.4
D8: D8.1, R20.2, REMOTE.3
D9: D9.1, R19.2, REMOTE.2
EFFECTS_L: MCRJ3.6, R6.2
EFFECTS_R: MCRJ3.4, R5.2
EFFECTS_RV12: MCRJ3.1, P1.3
EFFECTS_RVR: MCRJ3.3, P1.1
EFFECTS_RVS: MCRJ3.2, P1.2
GND: C1.2, C2.2, C3.2, C5.2, C8.1, C9.2, C10.2, C11.2, C12.2, C13.2, C14.2, C15.2, C16.2, C17.1, C18.2, C19.2, CR2450.2, CSDJ2.1, CSDJ2.5, CSDJ3.1, D1.2, D5.2, D6.2, D7.2, D8.2, D9.2, JAMMA.1, JAMMA.2, JAMMA.14, JAMMA.28, JAMMA.A, JAMMA.B, JAMMA.L, JAMMA.f, MCRJ1.1, MCRJ1.2, MCRJ1.3, MCRJ1.4, MCRJ1.5, MCRJ3.5, P3.3, R1.2, R9.2, R12.2, R13.1, REMOTE.1, TEST.2, U1.7, U2.7, U3.7, U4.7, U5.8, U5.9, U6.1, U6.8, U6.9, U6.15, U7.1, U8.8, U8.15, U9.8, U9.15, U10.1, U11.2, U11.4, U12.2, U12.8
J5_ST0: CSDJ1.5, MCR J5 - LAMPS.5
MAXMIN_CTEN: U5.4, U5.12, U6.4
MUSIC_L: CSDJ3.6, R7.2
MUSIC_R: CSDJ3.5, R8.2
MUSIC_RV12: CSDJ3.3, P2.3
MUSIC_RVR: CSDJ3.2, P2.1
MUSIC_RVS: CSDJ3.4, P2.2
Q0: MCRJ5.1, U8.4
Q1: MCRJ5.2, U8.7
Q2: MCRJ5.3, U8.12
Q3: MCRJ5.4, U8.9
Q4: MCRJ5.5, U9.4
Q5: MCRJ5.6, U9.7
Q6: MCRJ5.7, U9.12
Q7: MCRJ5.8, U9.9
RST: D4.2, R10.1, U3.4, U3.5, U10.3
RST_LED: D1.1, R10.2
SEL: MCRJ5.9, U4.1, U4.2
SERVICE_SW: JAMMA.R, MCRJ4.4
SHIFT_LATCH: MCRJ4.3, U2.5
TEST_SW: MCRJ4.5, TEST.1
U2_CLK: U2.3, U3.8
U6_RCO: U5.14, U6.13
U7_CTL: C3.1, U7.5
U7_DIS: R2.1, R3.1, U7.7
U7_DIS_P4_1: P4.1, R3.2
U7_RESET: D10.1, R1.1, U7.4
U7_TRIG: C1.1, P4.2, U7.2, U7.6
U8_I0a: U6.3, U8.2
U8_I0b: U6.2, U8.5
U8_I0c: U6.6, U8.14
U8_I0d: U6.7, U8.11
U9_I0a: U5.3, U9.2
U9_I0b: U5.2, U9.5
U9_I0c: U5.6, U9.14
U9_I0d: U5.7, U9.11
U10_CTL: C10.1, U10.5
U10_TRIG: C9.1, R11.1, U10.2, U10.6
U11_BYPASS: C5.1, U11.7
U11_GAIN_P1: C4.1, U11.1
U11_GAIN_P8: C4.2, U11.8
U12_A0: CSDJ1.1, MCR J5 - LAMPS.1, U12.5
U12_A1: CSDJ1.2, MCR J5 - LAMPS.2, U12.6
U12_A2: CSDJ1.3, MCR J5 - LAMPS.3, U12.7
U12_DATA: CSDJ1.4, MCR J5 - LAMPS.4, U12.3
U12_DISABLE: MCR J5 - LAMPS.6, U12.4
U12_Q0: R22.1, U12.9
U12_Q1: R23.1, U12.10
U12_Q2: R21.1, U12.11
U12_Q3: R20.1, U12.12
U12_Q4: R19.1, U12.13
V.BATT: D2.1, D3.1, MCRJ1.8
VIDEO_B: JAMMA.13, MCRJ2.3
VIDEO_G: JAMMA.N, MCRJ2.2
VIDEO_HSYNC: MCRJ2.4, U1.5
VIDEO_NXOR: R16.1, U1.3
VIDEO_R: JAMMA.12, MCRJ2.1
VIDEO_SYNC_OUT: JAMMA.P, R16.2
VIDEO_VSYNC: MCRJ2.5, U1.4
VIDEO_XOR: U1.2, U1.6

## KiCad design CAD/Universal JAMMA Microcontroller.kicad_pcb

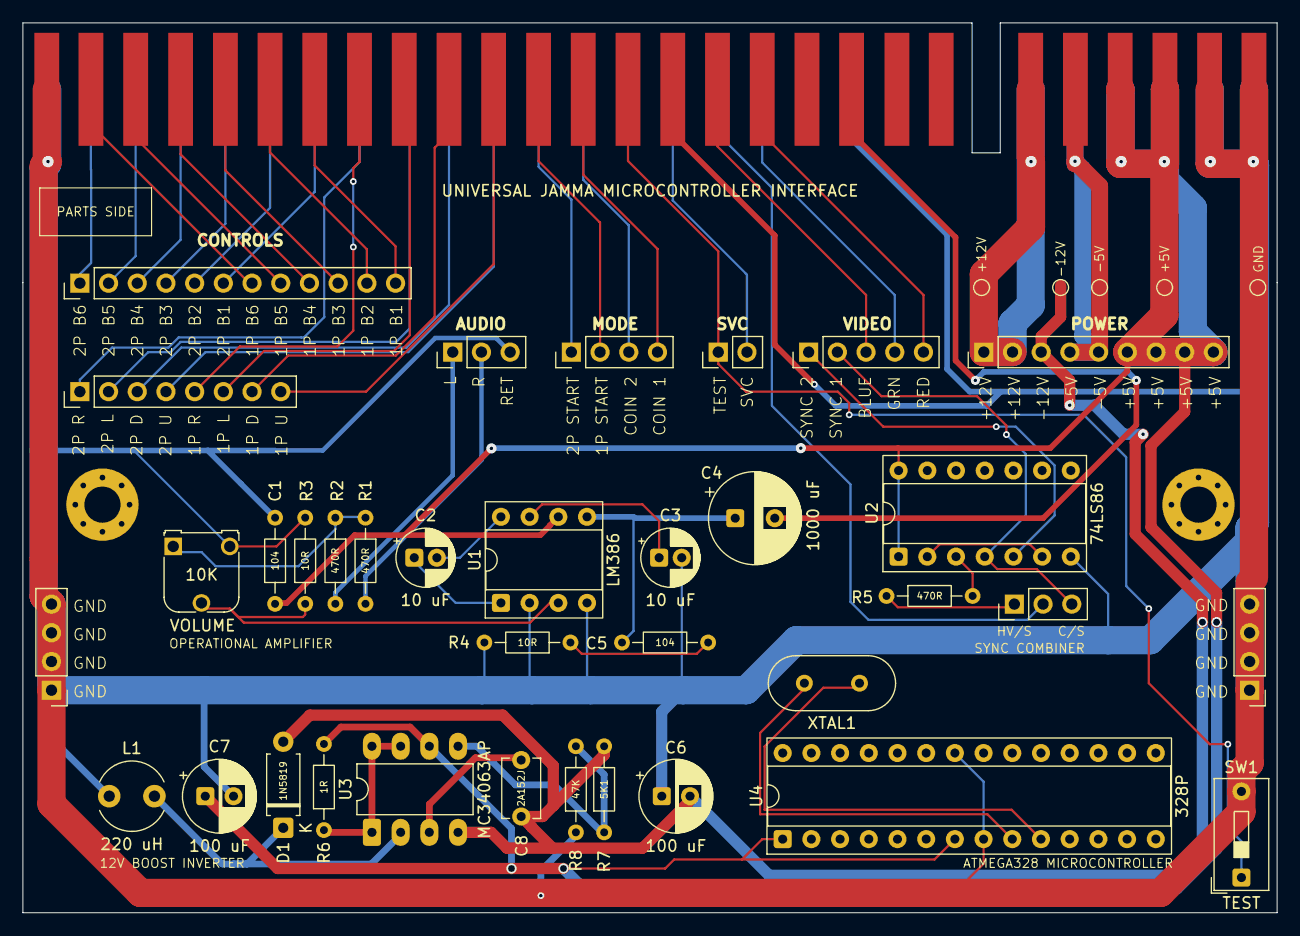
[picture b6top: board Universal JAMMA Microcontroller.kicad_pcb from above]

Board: 2 copper layers, 111.0 x 78.8 mm, 41 parts (0 on the bottom side), 56 nets.

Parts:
+5V, +12V: TestPoint_Pad_D1.0mm
-5V, -12V: TestPoint_Pad_D1.0mm
AUDIO: PinHeader_1x03_P2.54mm_Vertical
C1, C5: 104; R_Axial_DIN0204_L3.6mm_D1.6mm_P7.62mm_Horizontal
C2, C3: 10 uF; CP_Radial_D5.0mm_P2.00mm
C4: 1000 uF; CP_Radial_D8.0mm_P3.50mm
C6, C7: 100 uF; CP_Radial_D6.3mm_P2.50mm
C8: 2A152J; C_Disc_D5.1mm_W3.2mm_P5.00mm
CONTROLS: PinHeader_1x12_P2.54mm_Vertical
D1: 1N5819; D_A-405_P7.62mm_Horizontal
DIRECTIONALS: PinHeader_1x08_P2.54mm_Vertical
GND: TestPoint_Pad_D1.0mm
Ground: PinHeader_1x04_P2.54mm_Vertical
Ground#2: PinHeader_1x04_P2.54mm_Vertical
HV/S: PinHeader_1x03_P2.54mm_Vertical
JAMMA: HDR_JAMMA_56P_EDGE_CONNECTOR
L1: 220 uH; L_Radial_D6.0mm_P4.00mm
MODE: PinHeader_1x04_P2.54mm_Vertical
POWER: PinHeader_1x09_P2.54mm_Vertical
R1, R2, R5: 470R; R_Axial_DIN0204_L3.6mm_D1.6mm_P7.62mm_Horizontal
R3, R4: 10R; R_Axial_DIN0204_L3.6mm_D1.6mm_P7.62mm_Horizontal
R6: 1R; R_Axial_DIN0204_L3.6mm_D1.6mm_P7.62mm_Horizontal
R7: 5K1; R_Axial_DIN0204_L3.6mm_D1.6mm_P7.62mm_Horizontal
R8: 47K; R_Axial_DIN0204_L3.6mm_D1.6mm_P7.62mm_Horizontal
SVC: PinHeader_1x02_P2.54mm_Vertical
TEST: SW1; SW_DIP_SPSTx01_Slide_9.78x4.72mm_W7.62mm_P2.54mm
U1: LM386; DIP-8_W7.62mm_Socket
U2: 74LS86; DIP-14_W7.62mm_Socket
U3: MC34063AP; DIP-8_W7.62mm_LongPads
U4: 328P; DIP-28_W7.62mm_Socket
VIDEO: PinHeader_1x05_P2.54mm_Vertical
VOLUME: 10K; Potentiometer_Runtron_RM-065_Vertical
XTAL1: Crystal_HC49-4H_Vertical

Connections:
1P_B1: CONTROLS.12, JAMMA.22
1P_B2: CONTROLS.11, JAMMA.23
1P_B3: CONTROLS.10, JAMMA.24
1P_B4: CONTROLS.9, JAMMA.25
1P_B5: CONTROLS.8, JAMMA.26
1P_B6: CONTROLS.7, JAMMA.27
1P_D: DIRECTIONALS.7, JAMMA.19
1P_L: DIRECTIONALS.6, JAMMA.20
1P_R: DIRECTIONALS.5, JAMMA.21
1P_START: JAMMA.17, MODE.2
1P_U: DIRECTIONALS.8, JAMMA.18
2P_B1: CONTROLS.6, JAMMA.Z
2P_B2: CONTROLS.5, JAMMA.a
2P_B3: CONTROLS.4, JAMMA.b
2P_B4: CONTROLS.3, JAMMA.c
2P_B5: CONTROLS.2, JAMMA.d
2P_B6: CONTROLS.1, JAMMA.e
2P_D: DIRECTIONALS.3, JAMMA.W
2P_L: DIRECTIONALS.2, JAMMA.X
2P_R: DIRECTIONALS.1, JAMMA.Y
2P_START: JAMMA.U, MODE.1
2P_U: DIRECTIONALS.4, JAMMA.V
+5V: +5V.1, C1.1, C7.1, JAMMA.3, JAMMA.4, JAMMA.C, JAMMA.D, POWER.6, POWER.7, POWER.8, POWER.9, R6.2, U1.6, U2.1, U2.14, U3.6, U4.1, U4.7
+12V: +12V.1, JAMMA.6, JAMMA.F, POWER.1, POWER.2
-5V: -5V.1, JAMMA.5, JAMMA.E, POWER.4, POWER.5
-12V: -12V.1, C6.2, C8.1, D1.2, POWER.3, R7.2, U3.4
AUDIO_L: AUDIO.1, R2.2
AUDIO_MONO: R1.1, R2.1, VOLUME.1
AUDIO_R: AUDIO.2, R1.2
C5_R4: C5.1, R4.1
CINV_R7_R8: R7.1, R8.2, U3.5
COIN_1: JAMMA.16, MODE.4
COIN_2: JAMMA.T, MODE.3
GND: AUDIO.3, C1.2, C3.2, C6.1, C7.2, GND.1, Ground.1, Ground.2, Ground.3, Ground.4, Ground#2.1, Ground#2.2, Ground#2.3, Ground#2.4, JAMMA.1, JAMMA.2, JAMMA.14, JAMMA.28, JAMMA.A, JAMMA.B, JAMMA.L, JAMMA.f, L1.1, R3.2, R4.2, R8.1, TEST.2, U1.2, U1.4, U2.7, U4.8, U4.22, VOLUME.3
PB6: U4.9, XTAL1.2
PB7: U4.10, XTAL1.1
PREAMP: R3.1, U1.3, VOLUME.2
PREAMP_OUT: C4.1, C5.2, U1.5
R6: R6.1, U3.1, U3.7, U3.8
SERVICE: JAMMA.R, SVC.2
SPKR+: C4.2, JAMMA.10
SWE: D1.1, L1.2, U3.2
TEST: JAMMA.15, SVC.1, TEST.1
U3_CAP: C8.2, U3.3
U4_BYPASS: C3.1, U1.7
U4_GAIN_P1: C2.1, U1.1
U4_GAIN_P8: C2.2, U1.8
VID_B: JAMMA.13, VIDEO.3
VID_CSYNC: HV/S.2, JAMMA.P
VID_G: JAMMA.N, VIDEO.4
VID_NXOR: HV/S.1, R5.1
VID_NXOR_R5: R5.2, U2.3
VID_R: JAMMA.12, VIDEO.5
VID_SYN1: HV/S.3, U2.4, VIDEO.2
VID_SYN2: U2.5, VIDEO.1
VID_XOR: U2.2, U2.6

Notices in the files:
CAD/Atari JAMMA Interface.kicad_pcb:
PCB Design Copyright © 2025, Jonathan Zdziarski
All Rights Reserved
CAD/Spy Hunter JAMMA Adapter.kicad_pcb:
PCB Design Copyright © 2025, Jonathan Zdziarski. All Rights Reserved.
CAD/Super Hang-On JAMMA Adapter.kicad_pcb:
PCB Design Copyright © 2026, Jonathan Zdziarski
